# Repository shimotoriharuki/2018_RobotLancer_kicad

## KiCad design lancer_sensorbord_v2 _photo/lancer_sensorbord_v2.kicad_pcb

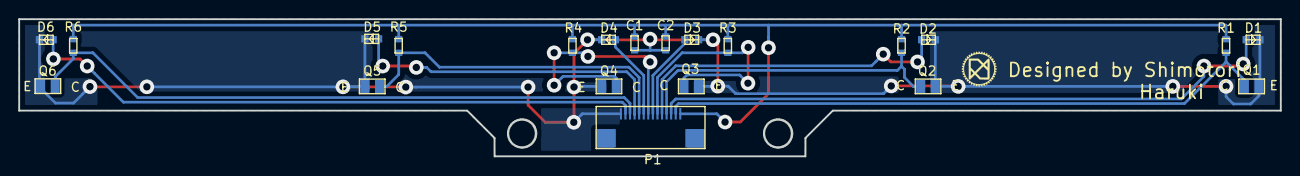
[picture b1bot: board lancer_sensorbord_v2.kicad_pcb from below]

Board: 2 copper layers, 138.0 x 15.0 mm, 21 parts (20 on the bottom side), 14 nets.

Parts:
C1, C2: 0.1u; C_1608_HandSolderring
D1, D2, D3, D4, D5, D6: SIR19-21C/TR8; SIR19-21C
P1: CN-FFC(0.5)14PD; CN-FFC-SMT2(CN-FFC(0.5)14PD)
Q1, Q2, Q3, Q4, Q5, Q6: TEMT7100X01
R1, R2, R3, R4, R5, R6: 100k; C_1608_HandSolderring

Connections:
+3V3: C1.1, C2.1, P1.1, R1.1, R2.1, R3.1, R4.1, R5.1, R6.1
ANALOG_SEN1: P1.2, Q1.2, R1.2
ANALOG_SEN2: P1.4, Q2.2, R2.2
ANALOG_SEN3: P1.6, Q3.2, R3.2
ANALOG_SEN4: P1.8, Q4.2, R4.2
ANALOG_SEN5: P1.10, Q5.2, R5.2
ANALOG_SEN6: P1.12, Q6.2, R6.2
GND: C1.2, C2.2, D1.1, D2.1, D3.1, D4.1, D5.1, D6.1, P1.14, Q1.1, Q2.1, Q3.1, Q4.1, Q5.1, Q6.1
VR1: D1.2, P1.3
VR2: D2.2, P1.5
VR3: D3.2, P1.7
VR4: D4.2, P1.9
VR5: D5.2, P1.11
VR6: D6.2, P1.13

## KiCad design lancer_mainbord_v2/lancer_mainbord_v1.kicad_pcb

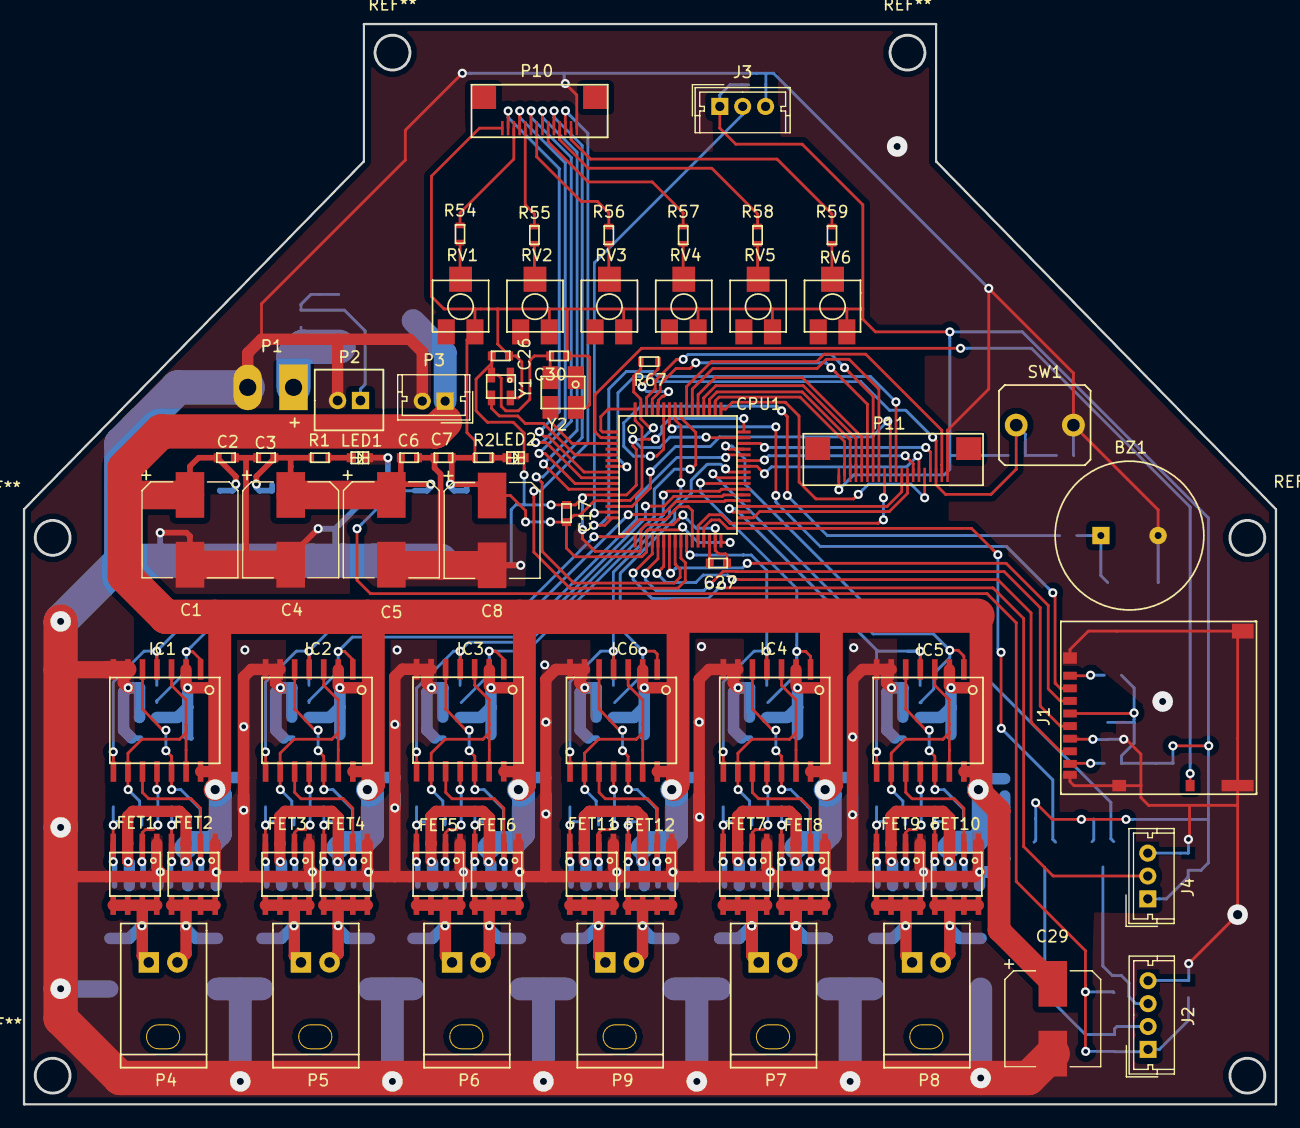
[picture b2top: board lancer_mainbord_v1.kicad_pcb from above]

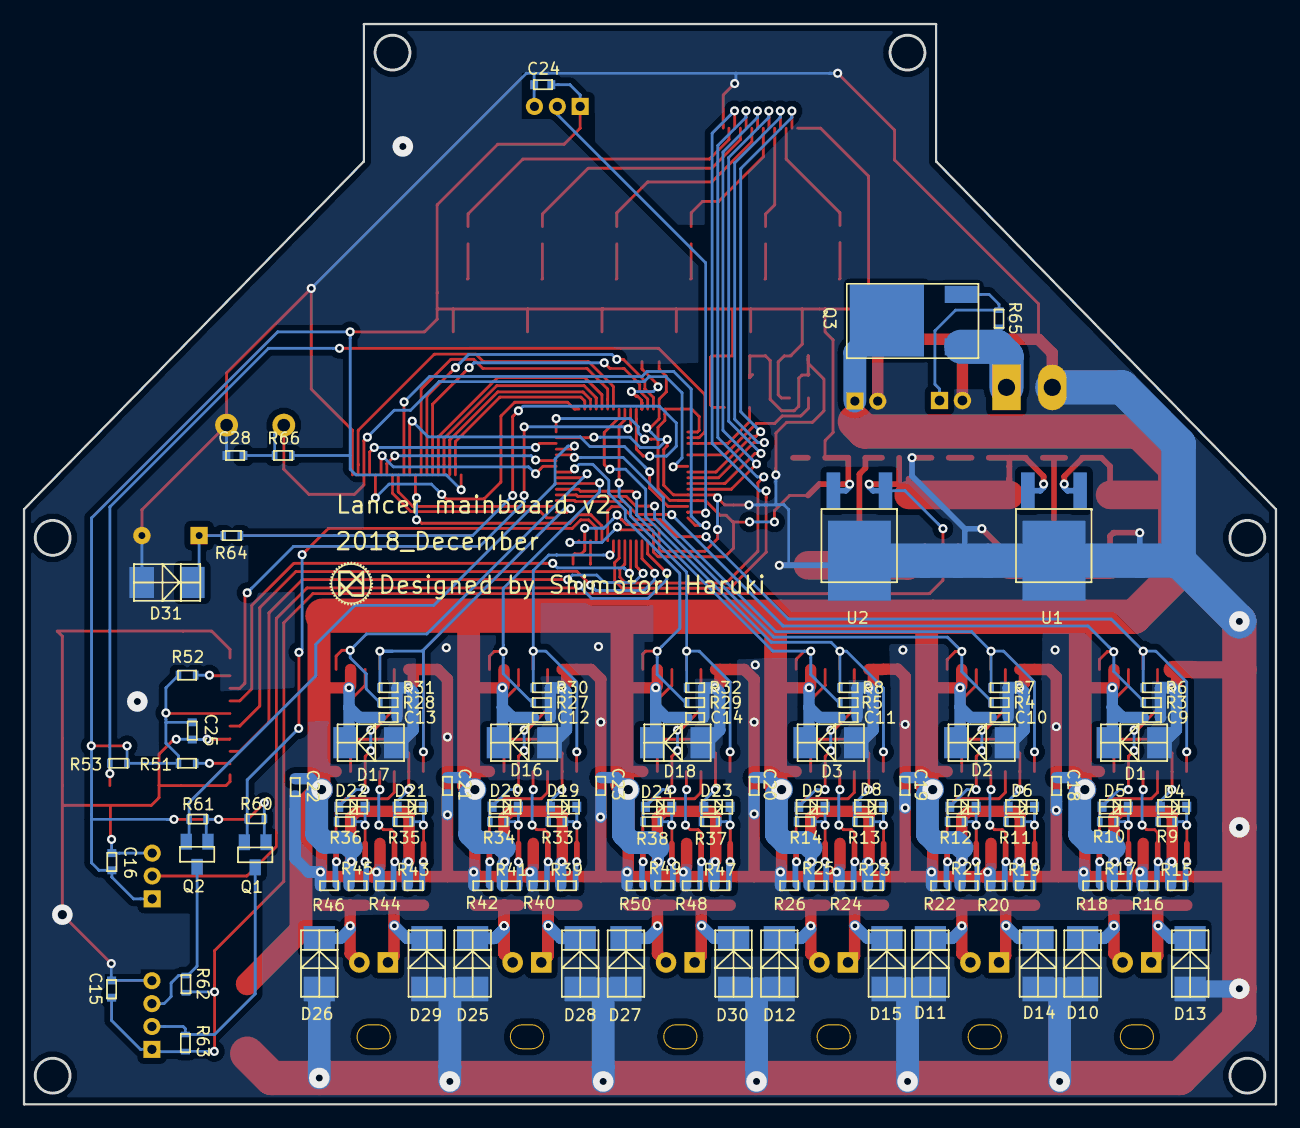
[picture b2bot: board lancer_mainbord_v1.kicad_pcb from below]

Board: 2 copper layers, 109.4 x 94.4 mm, 179 parts (113 on the bottom side), 123 nets.

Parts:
BZ1: PKM17EPP-4001-B0; PKM13EPYH4000-A0
C1, C4, C5, C8, C29: 220u; CP_Elec_8x10
C2, C3, C6, C7, C17, C25, C26, C30: 0.1u; C_1608_HandSolderring
C9, C10, C11, C12, C13, C14, C18, C19, C20, C21, C22, C23: 10u; C_1608_HandSolderring
C15, C16, C24, C28: 1u; C_1608_HandSolderring
C27: 4.7u; C_1608_HandSolderring
CPU1: STM32F401-64; stm32f401
D1, D2, D3, D10, D11, D12, D13, D14, D15, D16, D17, D18, D25, D26, D27, D28, D29, D30: 1SMB5930BT3G
D4, D5, D6, D7, D8, D9, D19, D20, D21, D22, D23, D24: CUS10F30
D31: 1SMB5919BT3G; 1SMB5930BT3G
FET1, FET2, FET3, FET4, FET5, FET6, FET7, FET8, FET9, FET10, FET11, FET12: TPC8407
IC1, IC2, IC3, IC4, IC5, IC6: TC4469
J1: Micro_SD_Card_Det; micro_SDcard
J2: encorder; Molex_MicroLatch-53253-0470_04x2.00mm_Straight
J3, J4: potentio; Molex_MicroLatch-53253-0370_03x2.00mm_Straight
LED1: 5V_CHECK; LED 1608
LED2: 3.3V_CHECK; LED 1608
P1: BATT; hole
P2: main_sw; PA_2pin
P3: VOLTAGE_CHECK; Molex_MicroLatch-53253-0270_02x2.00mm_Straight
P4, P5, P6, P7, P8, P9: XA_side; XA_2pin_boss
P10: CN-FFC-SMT2(CN-FFC(0.5)14PD)
P11: CN-FFC-SMT2(CN-FFC(0.5)22PD); CN-FFC-SMT2(CN-FFC(0.5)20PD)
Q1, Q2: Q_NMOS_GSD; BSS138
Q3: Q_PMOS_GDS; STD37P3H6AG
R1: 680; R_1608_HandSoldering
R2: 330; R_1608_HandSoldering
R3, R4, R5, R6, R7, R8, R15, R16, R17, R18, R19, R20, R21, R22, R23, R24, R25, R26, R27, R28, R29, R30, R31, R32, R39, R40, R41, R42, R43, R44, R45, R46, R47, R48, R49, R50, R65: 12k; R_1608_HandSoldering
R9, R10, R11, R12, R13, R14, R33, R34, R35, R36, R37, R38: 47; R_1608_HandSoldering
R51, R52, R53: 47k; R_1608_HandSoldering
R54, R55, R56, R57, R58, R59: 56; R_1608_HandSoldering
R60, R61, R62, R63, R67: 10k; R_1608_HandSoldering
R64: 1k; R_1608_HandSoldering
R66: 150k; R_1608_HandSoldering
RV1, RV2, RV3, RV4, RV5, RV6: 1k; G43ATB103
SW1: SW_Push; tact_switch
U1: NJM2845DL1-05; NJM2845DL1
U2: NJM2845DL1-33; NJM2845DL1
Y1: ASDMB-8.000MHZ-LY-T
Y2: ASEK-32.768KHZ-LRT

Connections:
+3V3: C7.1, C8.1, C16.1, C17.2, C24.1, C25.1, C26.1, C30.1, CPU1.1, CPU1.13, CPU1.19, CPU1.32, CPU1.48, CPU1.64, J1.4, J3.1, J4.1, P10.1, P11.1, Q1.1, Q2.1, R2.1, R51.1, R52.1, R53.1, R60.1, R61.1, R66.1, RV1.1, RV2.1, RV3.1, RV4.1, RV5.1, RV6.1, U2.3, Y1.4, Y2.4
+5V: C3.1, C4.1, C5.1, C6.1, C15.1, J2.1, R1.1, R62.1, R63.1, U1.3, U2.1
+12V: C1.1, C2.1, C9.1, C10.1, C11.1, C12.1, C13.1, C14.1, C18.1, C19.1, C20.1, C21.1, C22.1, C23.1, C29.1, D1.1, D2.1, D3.1, D16.1, D17.1, D18.1, FET1.3, FET2.3, FET3.3, FET4.3, FET5.3, FET6.3, FET7.3, FET8.3, FET9.3, FET10.3, FET11.3, FET12.3, IC1.1, IC1.3, IC1.15, IC1.16, IC2.1, IC2.3, IC2.15, IC2.16, IC3.1, IC3.3, IC3.15, IC3.16, IC4.1, IC4.3, IC4.15, IC4.16, IC5.1, IC5.3, IC5.15, IC5.16, IC6.1, IC6.3, IC6.15, IC6.16, P3.1, Q3.2, R15.1, R17.1, R19.1, R21.1, R23.1, R25.1, R39.1, R41.1, R43.1, R45.1, R47.1, R49.1, U1.1
ANALOG_SEN1: CPU1.8, P10.2
ANALOG_SEN2: CPU1.9, P10.4
ANALOG_SEN3: CPU1.10, P10.6
ANALOG_SEN4: CPU1.11, P10.8
ANALOG_SEN5: CPU1.24, P10.10
ANALOG_SEN6: CPU1.25, P10.12
BZ: CPU1.59, R64.1
CARD_DETECTION: CPU1.2, J1.10, R53.2
CS: CPU1.58, J1.2
DEBUG_LED1: CPU1.33, P11.13
DEBUG_LED2: CPU1.35, P11.12
DIR1: CPU1.36, IC1.2, R3.1
DIR2: CPU1.37, IC2.2, R4.1
DIR3: CPU1.38, IC3.2, R5.1
DIR4: CPU1.39, IC4.2, R27.1
DIR5: CPU1.40, IC5.2, R28.1
DIR6: CPU1.41, IC6.2, R29.1
ENCORDER_A: CPU1.29, Q1.2, R60.2
ENCORDER_B: CPU1.45, Q2.2, R61.2
GND: BZ1.2, C1.2, C2.2, C3.2, C4.2, C5.2, C6.2, C7.2, C8.2, C9.2, C10.2, C11.2, C12.2, C13.2, C14.2, C15.2, C16.2, C17.1, C18.2, C19.2, C20.2, C21.2, C22.2, C23.2, C24.2, C25.2, C26.2, C27.2, C28.2, C29.2, C30.2, CPU1.12, CPU1.18, CPU1.31, CPU1.47, CPU1.63, D1.2, D2.2, D3.2, D10.2, D11.2, D12.2, D13.2, D14.2, D15.2, D16.2, D17.2, D18.2, D25.2, D26.2, D27.2, D28.2, D29.2, D30.2, D31.2, FET1.1, FET2.1, FET3.1, FET4.1, FET5.1, FET6.1, FET7.1, FET8.1, FET9.1, FET10.1, FET11.1, FET12.1, IC1.7, IC1.8, IC2.7, IC2.8, IC3.7, IC3.8, IC4.7, IC4.8, IC5.7, IC5.8, IC6.7, IC6.8, J1.6, J1.9, J1.11, J1.12, J1.13, J1.14, J2.4, J3.3, J4.3, LED1.1, LED2.1, P1.2, P2.2, P3.2, P10.14, P11.20, R3.2, R4.2, R5.2, R6.2, R7.2, R8.2, R16.1, R18.1, R20.1, R22.1, R24.1, R26.1, R27.2, R28.2, R29.2, R30.2, R31.2, R32.2, R40.1, R42.1, R44.1, R46.1, R48.1, R50.1, R67.2, SW1.1, U1.2, U2.2, Y1.2, Y2.2
LANCE_PWM: CPU1.57, IC6.5, IC6.9, R32.1
LB_PWM: CPU1.44, IC2.5, IC2.9, R7.1
LF_PWM: CPU1.27, IC1.5, IC1.9, R6.1
MISO: CPU1.22, J1.7
MOSI: CPU1.23, J1.3
NRST: C28.1, CPU1.7, P11.18, R66.2, SW1.2
unnamed: BZ1.1, D31.1, R64.2
unnamed: C27.1, CPU1.30
unnamed: CPU1.60, R67.1
unnamed: D4.1, FET1.4, R9.1, R15.2
unnamed: D4.2, IC1.4, IC1.10, IC1.14, R9.2
unnamed: D5.1, FET2.4, R10.1, R17.2
unnamed: D5.2, IC1.6, IC1.13, R10.2
unnamed: D6.1, FET3.4, R11.1, R19.2
unnamed: D6.2, IC2.4, IC2.10, IC2.14, R11.2
unnamed: D7.1, FET4.4, R12.1, R21.2
unnamed: D7.2, IC2.6, IC2.13, R12.2
unnamed: D8.1, FET5.4, R13.1, R23.2
unnamed: D8.2, IC3.4, IC3.10, IC3.14, R13.2
unnamed: D9.1, FET6.4, R14.1, R25.2
unnamed: D9.2, IC3.6, IC3.13, R14.2
unnamed: D10.1, FET2.5, FET2.6, FET2.7, FET2.8, P4.2
unnamed: D11.1, FET4.5, FET4.6, FET4.7, FET4.8, P5.2
unnamed: D12.1, FET6.5, FET6.6, FET6.7, FET6.8, P6.2
unnamed: D13.1, FET1.5, FET1.6, FET1.7, FET1.8, P4.1
unnamed: D14.1, FET3.5, FET3.6, FET3.7, FET3.8, P5.1
unnamed: D15.1, FET5.5, FET5.6, FET5.7, FET5.8, P6.1
unnamed: D19.1, FET7.4, R33.1, R39.2
unnamed: D19.2, IC4.4, IC4.10, IC4.14, R33.2
unnamed: D20.1, FET8.4, R34.1, R41.2
unnamed: D20.2, IC4.6, IC4.13, R34.2
unnamed: D21.1, FET9.4, R35.1, R43.2
unnamed: D21.2, IC5.4, IC5.10, IC5.14, R35.2
unnamed: D22.1, FET10.4, R36.1, R45.2
unnamed: D22.2, IC5.6, IC5.13, R36.2
unnamed: D23.1, FET11.4, R37.1, R47.2
unnamed: D23.2, IC6.4, IC6.10, IC6.14, R37.2
unnamed: D24.1, FET12.4, R38.1, R49.2
unnamed: D24.2, IC6.6, IC6.13, R38.2
unnamed: D25.1, FET8.5, FET8.6, FET8.7, FET8.8, P7.2
unnamed: D26.1, FET10.5, FET10.6, FET10.7, FET10.8, P8.2
unnamed: D27.1, FET12.5, FET12.6, FET12.7, FET12.8, P9.2
unnamed: D28.1, FET7.5, FET7.6, FET7.7, FET7.8, P7.1
unnamed: D29.1, FET9.5, FET9.6, FET9.7, FET9.8, P8.1
unnamed: D30.1, FET11.5, FET11.6, FET11.7, FET11.8, P9.1
unnamed: FET1.2, IC1.12, R16.2
unnamed: FET2.2, IC1.11, R18.2
unnamed: FET3.2, IC2.12, R20.2
unnamed: FET4.2, IC2.11, R22.2
unnamed: FET5.2, IC3.12, R24.2
unnamed: FET6.2, IC3.11, R26.2
unnamed: FET7.2, IC4.12, R40.2
unnamed: FET8.2, IC4.11, R42.2
unnamed: FET9.2, IC5.12, R44.2
unnamed: FET10.2, IC5.11, R46.2
unnamed: FET11.2, IC6.12, R48.2
unnamed: FET12.2, IC6.11, R50.2
unnamed: J1.1, R52.2
unnamed: J1.8, R51.2
unnamed: J2.2, Q1.3, R63.2
unnamed: J2.3, Q2.3, R62.2
unnamed: LED1.2, R1.2
unnamed: LED2.2, R2.2
unnamed: P1.1, Q3.1, R65.1
unnamed: P2.1, Q3.3, R65.2
unnamed: P10.3, R54.1
unnamed: P10.5, R55.1
unnamed: P10.7, R56.1
unnamed: P10.9, R57.1
unnamed: P10.11, R58.1
unnamed: P10.13, R59.1
unnamed: R54.2, RV1.2
unnamed: R55.2, RV2.2
unnamed: R56.2, RV3.2
unnamed: R57.2, RV4.2
unnamed: R58.2, RV5.2
unnamed: R59.2, RV6.2
OSC_IN: CPU1.5, Y1.3
POTENTIOMETER1: CPU1.15, J3.2
POTENTIOMETER2: CPU1.20, J4.2
RB_PWM: CPU1.34, IC5.5, IC5.9, R31.1
RF_PWM: CPU1.26, IC4.5, IC4.9, R30.1
RTC_IN: CPU1.3, Y2.3
RX: CPU1.43, P11.14
R_SW1: CPU1.50, P11.2
R_SW2: CPU1.51, P11.3
R_SW4: CPU1.52, P11.4
R_SW8: CPU1.53, P11.5
SCK: CPU1.21, J1.5
SCL: CPU1.61, P11.6
SDA: CPU1.62, P11.7
SWO: CPU1.55, P11.19
S_PWM: CPU1.56, IC3.5, IC3.9, R8.1
TACT_SW1: CPU1.16, P11.11
TACT_SW2: CPU1.14, P11.10
TACT_SW3: CPU1.28, P11.9
TACT_SW4: CPU1.54, P11.8
TCK: CPU1.49, P11.16
TMS: CPU1.46, P11.17
TX: CPU1.42, P11.15

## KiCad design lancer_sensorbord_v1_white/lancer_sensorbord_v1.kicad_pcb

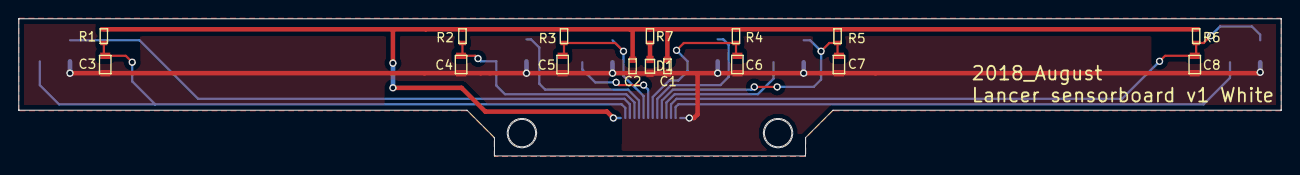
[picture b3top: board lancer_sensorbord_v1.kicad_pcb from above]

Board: 2 copper layers, 138.0 x 15.0 mm, 23 parts (0 on the bottom side), 15 nets.

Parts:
C1, C2: 0.1u; C_1608_HandSolderring_1000pF
C3, C4, C5, C6, C7, C8: 1000p; C_2012_HandSolderring_0.1u
D1: LED_ALT; LED 1608
LineSensor: CN-FFC-SMT2(CN-FFC(0.5)14PD)
PI1, PI2, PI3, PI4, PI5, PI6: GP2S700HCP
R1, R2, R3, R4, R5, R6: 100k; R_1608_HandSoldering
R7: 330; R_1608_HandSoldering

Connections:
+3V3: C1.1, C2.1, LineSensor.1, R1.1, R2.1, R3.1, R4.1, R5.1, R6.1, R7.1
ANALOG_SEN1: C3.1, LineSensor.2, PI1.2, R1.2
ANALOG_SEN2: C4.1, LineSensor.4, PI2.2, R2.2
ANALOG_SEN3: C5.1, LineSensor.6, PI3.2, R3.2
ANALOG_SEN4: C6.1, LineSensor.8, PI4.2, R4.2
ANALOG_SEN5: C7.1, LineSensor.10, PI5.2, R5.2
ANALOG_SEN6: C8.1, LineSensor.12, PI6.2, R6.2
GND: C1.2, C2.2, C3.2, C4.2, C5.2, C6.2, C7.2, C8.2, D1.1, LineSensor.14, PI1.1, PI1.3, PI2.1, PI2.3, PI3.1, PI3.3, PI4.1, PI4.3, PI5.1, PI5.3, PI6.1, PI6.3
unnamed: D1.2, R7.2
VR1: LineSensor.3, PI1.4
VR2: LineSensor.5, PI2.4
VR3: LineSensor.7, PI3.4
VR4: LineSensor.9, PI4.4
VR5: LineSensor.11, PI5.4
VR6: LineSensor.13, PI6.4

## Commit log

2021-03-22 init
2021-03-22 Create LICENSE
